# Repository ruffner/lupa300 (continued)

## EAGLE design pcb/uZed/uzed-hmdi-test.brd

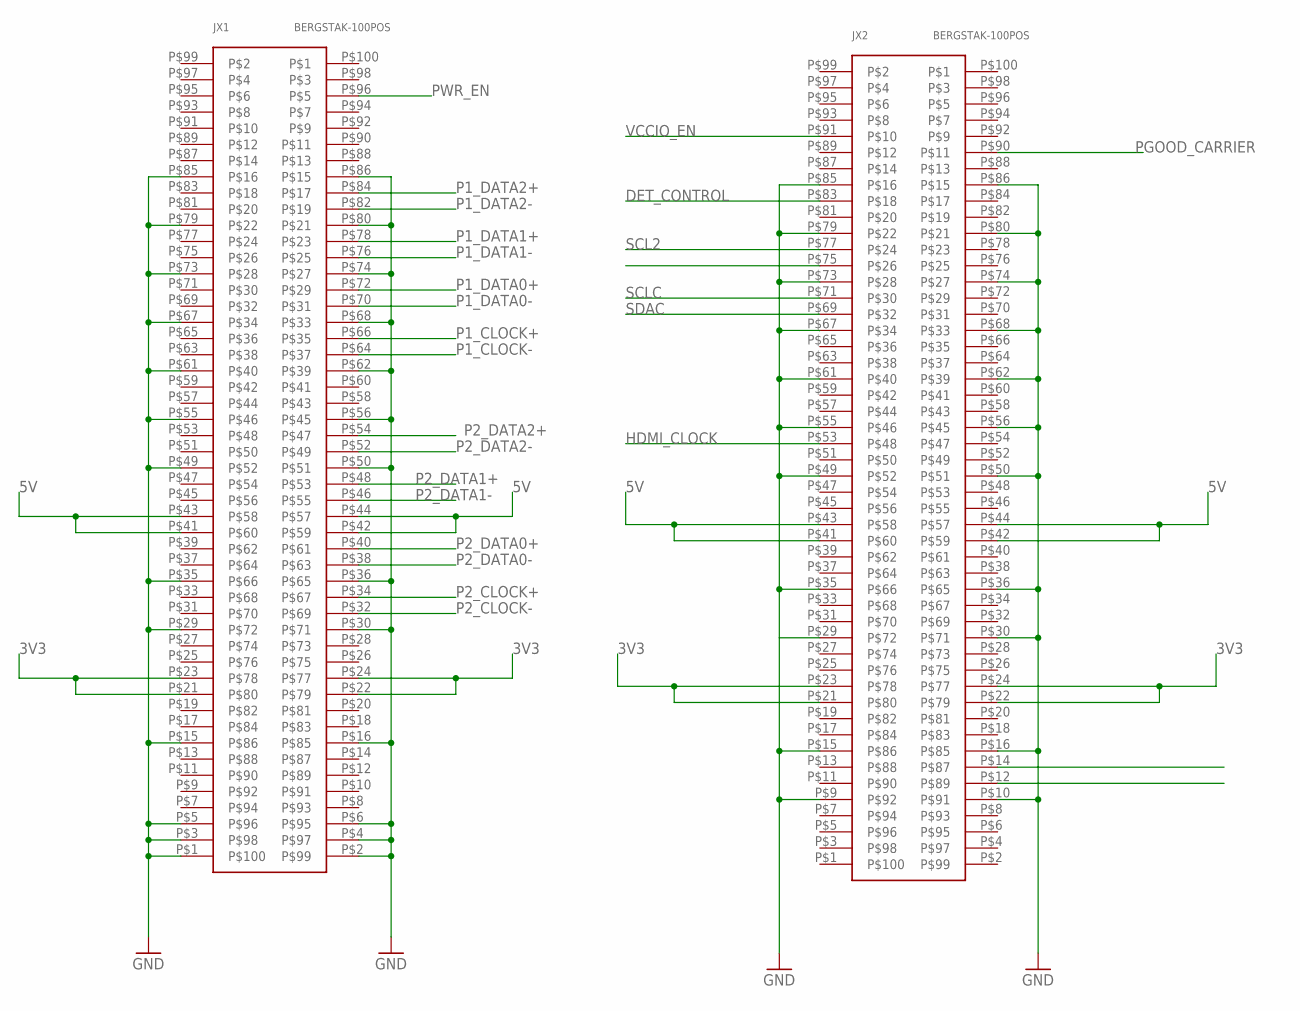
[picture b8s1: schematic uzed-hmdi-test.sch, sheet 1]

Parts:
JX1, JX2: BERGSTAK-100POS; BERG100POS

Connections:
3V3: JX1.P$21, JX1.P$22, JX1.P$23, JX1.P$24, JX2.P$21, JX2.P$22, JX2.P$23, JX2.P$24; also elsewhere on the board
5V: JX1.P$41, JX1.P$42, JX1.P$43, JX1.P$44, JX2.P$41, JX2.P$42, JX2.P$43, JX2.P$44; also elsewhere on the board
DET_CONTROL: JX2.P$83; also elsewhere on the board
GND: JX1.P$1, JX1.P$2, JX1.P$3, JX1.P$4, JX1.P$5, JX1.P$6, JX1.P$15, JX1.P$16, JX1.P$29, JX1.P$30, JX1.P$35, JX1.P$36, JX1.P$49, JX1.P$50, JX1.P$55, JX1.P$56, JX1.P$61, JX1.P$62, JX1.P$67, JX1.P$68, JX1.P$73, JX1.P$74, JX1.P$79, JX1.P$80, JX1.P$85, JX1.P$86, JX2.P$9, JX2.P$10, JX2.P$15, JX2.P$16, JX2.P$29, JX2.P$30, JX2.P$35, JX2.P$36, JX2.P$49, JX2.P$50, JX2.P$55, JX2.P$56, JX2.P$61, JX2.P$62, JX2.P$67, JX2.P$68, JX2.P$73, JX2.P$74, JX2.P$79, JX2.P$80, JX2.P$85, JX2.P$86; also elsewhere on the board
HDMI_CLOCK: JX2.P$53; also elsewhere on the board
P1_CLOCK+: JX1.P$66; also elsewhere on the board
P1_CLOCK-: JX1.P$64; also elsewhere on the board
P1_DATA0+: JX1.P$72; also elsewhere on the board
P1_DATA0-: JX1.P$70; also elsewhere on the board
P1_DATA1+: JX1.P$78; also elsewhere on the board
P1_DATA1-: JX1.P$76; also elsewhere on the board
P1_DATA2+: JX1.P$84; also elsewhere on the board
P1_DATA2-: JX1.P$82; also elsewhere on the board
P2_CLOCK+: JX1.P$34; also elsewhere on the board
P2_CLOCK-: JX1.P$32; also elsewhere on the board
P2_DATA0+: JX1.P$40; also elsewhere on the board
P2_DATA0-: JX1.P$38; also elsewhere on the board
P2_DATA1+: JX1.P$48; also elsewhere on the board
P2_DATA1-: JX1.P$46; also elsewhere on the board
P2_DATA2+: JX1.P$54; also elsewhere on the board
P2_DATA2-: JX1.P$52; also elsewhere on the board
PGOOD_CARRIER: JX2.P$90
PWR_EN: JX1.P$96
SCL2: JX2.P$77; also elsewhere on the board
SCLC: JX2.P$71; also elsewhere on the board
SDA2: JX2.P$75; also elsewhere on the board
SDAC: JX2.P$69; also elsewhere on the board
VCCIO_EN: JX2.P$91

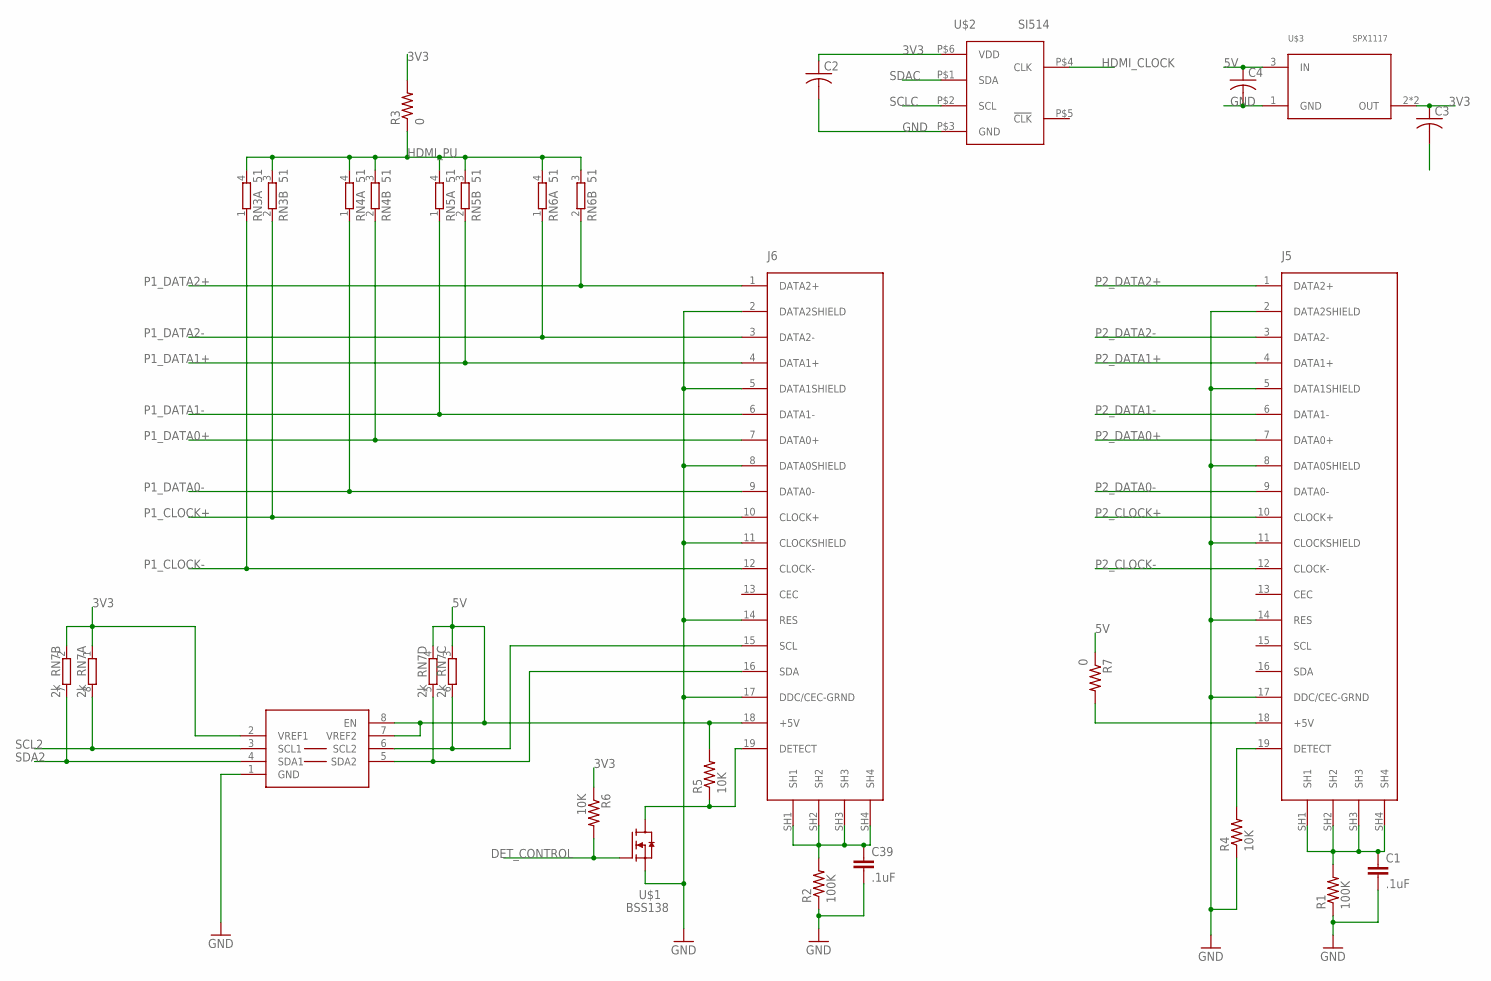
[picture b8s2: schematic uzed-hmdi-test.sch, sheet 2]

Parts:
C1, C39: .1uF; C0603K
C2, C3, C4: C-USC0603; C0603
J5, J6: HDMI-TYPE-A-RECEPTICALFCI10029449; FCI-HDMI-TYPE-A-RECEPT
PCA9306: PCA9306; PSOP-8
R1, R2: 100K; R0603
R3, R7: 0; R0603
R4, R5, R6: 10K; R0603
RN3, RN4, RN5, RN6: 51; EXB34V
RN7: 2k; 0603-ARV
U$1: BSS138; SOT23
U$2: SI514; XTAL-6PIN
U$3: SPX1117; SOT223

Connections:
3V3: C2.1, C3.1, PCA9306.2 (VREF1), R3.2, R6.1, RN7.1, RN7.2 (1), U$2.P$6 (VDD), U$3.2 (OUT), U$3.4 (OUT); also elsewhere on the board
5V: C4.1, J6.18 (+5V), PCA9306.7 (VREF2), PCA9306.8 (EN), R5.2, R7.1, RN7.3 (1), RN7.4 (1), U$3.3 (IN); also elsewhere on the board
DET_CONTROL: R6.2, U$1.1 (G); also elsewhere on the board
GND: C1.2, C2.2, C3.2, C4.2, C39.2, J5.2 (DATA2SHIELD), J5.5 (DATA1SHIELD), J5.8 (DATA0SHIELD), J5.11 (CLOCKSHIELD), J5.14 (RES), J5.17 (DDC/CEC-GRND), J6.2 (DATA2SHIELD), J6.5 (DATA1SHIELD), J6.8 (DATA0SHIELD), J6.11 (CLOCKSHIELD), J6.14 (RES), J6.17 (DDC/CEC-GRND), PCA9306.1 (GND), R1.1, R2.1, R4.1, U$1.2 (S), U$2.P$3 (GND), U$3.1 (GND); also elsewhere on the board
HDMI_CLOCK: U$2.P$4 (CLK); also elsewhere on the board
HDMI_PU: R3.1, RN3.3 (2), RN3.4 (2), RN4.3 (2), RN4.4 (2), RN5.3 (2), RN5.4 (2), RN6.3 (2), RN6.4 (2)
unnamed: C1.1, J5.SH1, J5.SH2, J5.SH3, J5.SH4, R1.2
unnamed: J5.19 (DETECT), R4.2
unnamed: J6.19 (DETECT), R5.1, U$1.3 (D)
unnamed: J5.18 (+5V), R7.2
unnamed: J6.16 (SDA), PCA9306.5 (SDA2), RN7.5 (2)
unnamed: J6.15 (SCL), PCA9306.6 (SCL2), RN7.6 (2)
unnamed: C39.1, J6.SH1, J6.SH2, J6.SH3, J6.SH4, R2.2
P1_CLOCK+: J6.10 (CLOCK+), RN3.2 (1); also elsewhere on the board
P1_CLOCK-: J6.12 (CLOCK-), RN3.1; also elsewhere on the board
P1_DATA0+: J6.7 (DATA0+), RN4.2 (1); also elsewhere on the board
P1_DATA0-: J6.9 (DATA0-), RN4.1; also elsewhere on the board
P1_DATA1+: J6.4 (DATA1+), RN5.2 (1); also elsewhere on the board
P1_DATA1-: J6.6 (DATA1-), RN5.1; also elsewhere on the board
P1_DATA2+: J6.1 (DATA2+), RN6.2 (1); also elsewhere on the board
P1_DATA2-: J6.3 (DATA2-), RN6.1; also elsewhere on the board
P2_CLOCK+: J5.10 (CLOCK+); also elsewhere on the board
P2_CLOCK-: J5.12 (CLOCK-); also elsewhere on the board
P2_DATA0+: J5.7 (DATA0+); also elsewhere on the board
P2_DATA0-: J5.9 (DATA0-); also elsewhere on the board
P2_DATA1+: J5.4 (DATA1+); also elsewhere on the board
P2_DATA1-: J5.6 (DATA1-); also elsewhere on the board
P2_DATA2+: J5.1 (DATA2+); also elsewhere on the board
P2_DATA2-: J5.3 (DATA2-); also elsewhere on the board
SCL2: PCA9306.3 (SCL1), RN7.8 (2); also elsewhere on the board
SCLC: U$2.P$2 (SCL); also elsewhere on the board
SDA2: PCA9306.4 (SDA1), RN7.7 (2); also elsewhere on the board
SDAC: U$2.P$1 (SDA); also elsewhere on the board

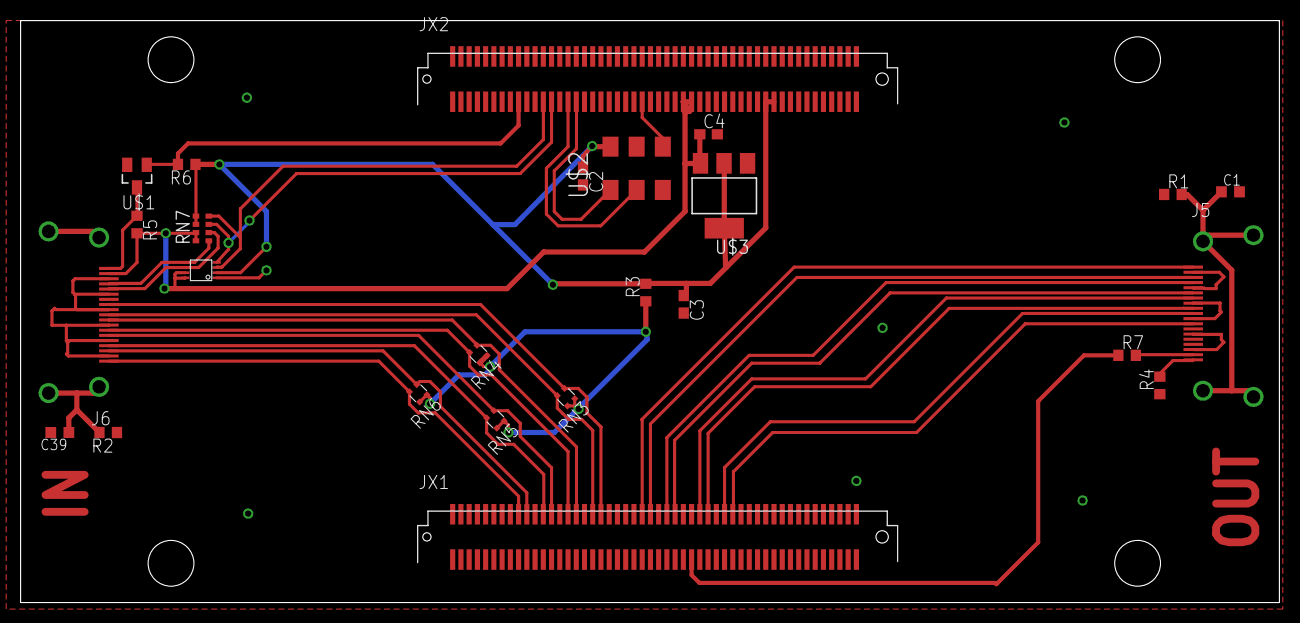
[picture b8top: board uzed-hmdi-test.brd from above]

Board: 2 copper layers, 122.2 x 56.5 mm, 25 parts (0 on the bottom side), 33 nets.

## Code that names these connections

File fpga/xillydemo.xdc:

# There are no constraints in this XDC file, because
#
# (a) the only clock in the system is generated by the processor part, and
#     it's already constrained through generated XDCs, and
# (b) there are no pin placements, since the board has nothing connected to
#     the PL pins, except for general-purpose expansion connectors.


set_property IOSTANDARD LVCMOS25 [get_ports {DATA_IMAGE[9]}]
set_property IOSTANDARD LVCMOS25 [get_ports {DATA_IMAGE[8]}]
set_property IOSTANDARD LVCMOS25 [get_ports {DATA_IMAGE[7]}]
set_property IOSTANDARD LVCMOS25 [get_ports {DATA_IMAGE[6]}]
set_property IOSTANDARD LVCMOS25 [get_ports {DATA_IMAGE[5]}]
set_property IOSTANDARD LVCMOS25 [get_ports {DATA_IMAGE[4]}]
set_property IOSTANDARD LVCMOS25 [get_ports {DATA_IMAGE[3]}]
set_property IOSTANDARD LVCMOS25 [get_ports {DATA_IMAGE[2]}]
set_property IOSTANDARD LVCMOS25 [get_ports {DATA_IMAGE[1]}]
set_property IOSTANDARD LVCMOS25 [get_ports {DATA_IMAGE[0]}]
set_property PACKAGE_PIN R19 [get_ports {DATA_IMAGE[9]}]
set_property PACKAGE_PIN T11 [get_ports {DATA_IMAGE[8]}]
set_property PACKAGE_PIN T12 [get_ports {DATA_IMAGE[7]}]
set_property PACKAGE_PIN T10 [get_ports {DATA_IMAGE[6]}]
set_property PACKAGE_PIN T19 [get_ports {DATA_IMAGE[5]}]
set_property PACKAGE_PIN U12 [get_ports {DATA_IMAGE[4]}]
set_property PACKAGE_PIN V12 [get_ports {DATA_IMAGE[3]}]
set_property PACKAGE_PIN U13 [get_ports {DATA_IMAGE[2]}]
set_property IOSTANDARD LVCMOS25 [get_ports FRAME_VALID]
set_property IOSTANDARD LVCMOS33 [get_ports INT_TIME1]
set_property IOSTANDARD LVCMOS33 [get_ports INT_TIME2]
set_property IOSTANDARD LVCMOS33 [get_ports INT_TIME3]
set_property IOSTANDARD LVCMOS25 [get_ports LINE_VALID]
set_property IOSTANDARD LVCMOS33 [get_ports LUPA_CLK]
set_property IOSTANDARD LVCMOS33 [get_ports LUPA_RST]
set_property IOSTANDARD LVCMOS25 [get_ports SPI_CLK]
set_property IOSTANDARD LVCMOS25 [get_ports SPI_DAT]
set_property IOSTANDARD LVCMOS25 [get_ports SPI_EN]
set_property PACKAGE_PIN C20 [get_ports LUPA_RST]
set_property PACKAGE_PIN D20 [get_ports LUPA_CLK]
set_property PACKAGE_PIN P14 [get_ports FRAME_VALID]
set_property PACKAGE_PIN T15 [get_ports LINE_VALID]


set_property PACKAGE_PIN Y16 [get_ports SPI_EN]
set_property PACKAGE_PIN W14 [get_ports SPI_CLK]
set_property PACKAGE_PIN Y17 [get_ports SPI_DAT]


set_property IOSTANDARD LVCMOS25 [get_ports {LED_debug[3]}]
set_property IOSTANDARD LVCMOS25 [get_ports {LED_debug[2]}]
set_property IOSTANDARD LVCMOS25 [get_ports {LED_debug[1]}]
set_property IOSTANDARD LVCMOS25 [get_ports {LED_debug[0]}]


set_property PACKAGE_PIN B19 [get_ports INT_TIME1]


set_property PACKAGE_PIN B20 [get_ports INT_TIME2]
set_property PACKAGE_PIN A20 [get_ports INT_TIME3]





set_property CLOCK_DEDICATED_ROUTE FALSE [get_nets FRAME_VALID_IBUF]
set_property CLOCK_DEDICATED_ROUTE FALSE [get_nets LINE_VALID_IBUF]
















set_property PULLUP true [get_ports LINE_VALID]
set_property PULLUP true [get_ports FRAME_VALID]




















set_property PULLUP true [get_ports SPI_CLK]
set_property PULLUP true [get_ports SPI_DAT]
set_property PULLUP true [get_ports SPI_EN]


set_property PACKAGE_PIN T16 [get_ports {LED_debug[0]}]
set_property PACKAGE_PIN V15 [get_ports {LED_debug[1]}]
set_property PACKAGE_PIN U17 [get_ports {LED_debug[2]}]
set_property PACKAGE_PIN W15 [get_ports {LED_debug[3]}]

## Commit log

2017-08-30 added pcb and lens mount
2017-08-31 setup inital firmware
2017-08-31 added pin defs
2017-12-05 started new breakout board
2017-12-06 more work on breakout
2017-12-07 finished lupa breakout
2017-12-08 increased via pad size
2017-12-08 made passices 1206 form factor
2017-12-08 started on lupa carrier:
2017-12-14 work on carrier
2017-12-14 work on lup breakout
2017-12-14 added newer soft start board for pin reference, removed old dual header design
2017-12-14 finalized breakout for lupa module
2017-12-14 finished with uZed carrier board.
2017-12-14 added image of dimensioned breakout board
2017-12-14 bare bones qt application working
2017-12-15 made vias smaller and fixed silkscreen
2017-12-15 fixed silkscreen
2017-12-15 started carrier board for teensy
2017-12-19 finished teensy carrier and added image of dimensions
2017-12-20 updated pin defs for teensy_carrier board
2018-01-19 updated lens mount
2018-01-19 created lupa sensor protective cover
2018-01-19 added mosfet for fpga control of board power
2018-01-25 added fixed focal length lens moount
2018-02-01 added new camera shield
2018-02-02 finished new camera shield
2018-02-03 started v2 lupa breakout, for microzed sbc
2018-02-04 more work on lupa card
2018-02-04 made lupa card 4 layer
2018-02-04 finished prelim routing.
2018-02-05 routed critical signals.
2018-02-05 finalized design
2018-02-05 added references and BOM for new 4 layer lupa card order
2018-02-06 removed eagle library backup files
2018-02-13 added bergstak 100 pin connector to eagle library and started uzed hdmi shield
2018-02-19 added all component values and added partslist
2018-03-02 added new pluto fpga camer trigger shield
2018-03-05 made a home for all the cad
2018-03-06 updated pluto enclosure
2018-03-06 prog xtal breakout and work on hdmi board
2018-03-07 reorganized pcb folder
2018-03-08 moved lupa300 card
2018-03-09 added stl folder for lens mounts and added c mount bracket for the lupa300-card pcb
2018-03-13 upate trigger shield
2018-03-13 added pca9306 breakout
2018-03-18 added new board design
2018-03-19 added si514 programmer
2018-03-20 added code to program 73.25Mhz to xo. untested
2018-03-20 added new voltage regulators
2018-03-20 73.25 MHZ programming code verified, made general programming function
2018-03-21 more work
2018-03-25 added adc output buffer
2018-03-26 added separate ground planes
2018-03-26 added buffer
2018-03-28 hdmi connections copied in from scarab hardware board
2018-03-30 hdmi added in from scarab board
2018-03-30 added spdt switch and new n channel mosfet
2018-03-30 more work on hdmi, layout with mounting holes complete, bergstak connectors aligned to be to carrier board spec
2018-03-30 added reference layout documents and oder csv list
2018-03-30 added bergstak dimensional drawing
2018-03-30 added uZed carrier design guide
2018-03-30 improved register generating code. 73.5MHz is correct clock for 120.00 Hz video
2018-03-30 added minispartan reference designs
2018-04-04 added basler board
2018-04-04 added text
2018-04-06 started 2 layer hdmi test board
2018-04-09 more work on hdmi -test
2018-04-09 full sized hdmi test
2018-04-09 finished hdmi test board
2018-04-10 added pin connections for hdmi test board
2018-04-12 cleaned up and added more comments
2018-04-17 added mojo reference library
2018-04-17 added mojo basler begin
2018-04-18 finished basler camera adapter shield for mojo fpga board
2018-04-23 started dual basler shield for the mojo
2018-04-30 switched to full coverage shield with new pinouts
2018-05-07 added git ignore
2018-05-08 dual basler shield circuit complete
2018-05-08 dual basler shield silkscreen edit
2018-05-08 added manta manual for pinout
2018-05-08 added basler manual
2018-05-14 added lau logo
2018-05-14 started avt trigger board
2018-05-15 finished avt trigger board
2018-05-15 fixed pin assignments
2018-05-21 added test carrier design
2018-05-21 added new components for carrier board
2018-05-21 more work on carrier test
2018-05-21 more carrier card components added
2018-05-22 tweaked layout, ready to fab
2018-05-31 added 2A 3.3v reg to power suply design. made power supply layout more compact. increased board size
2018-06-01 more lupa crrier layout work
2018-06-02 almost done routing
2018-06-04 finished improved power supply layout
2018-06-04 arranged silk screen text.
2018-06-04 ordered 5 from pcbway as is
2018-06-05 started lupa300 integration, converted to 4 layer
2018-06-05 added andon library for lupa300 socket
2018-06-05 layout out power for lupa
2018-06-06 added low noise regulators for sensitive lupa supplys
2018-06-12 layed out regualtors for lupa power
2018-06-19 more work on power supply to lupa
2018-06-19 more work on power routing
2018-06-20 started clock and data pin routing
2018-06-27 more work on power dist
2018-06-28 control lines layed out. pdn complete.
2018-06-29 almost ready for fab
2018-07-02 ordered from pcbway
2018-07-17 added partslist for lupa carrier board
2018-07-23 added lupa-carrier cover and lens mount
2018-07-26 added hdmi connectors, routing in progress
2018-07-27 started hdmi integration. removed dot in drill layer in andon socket
2018-07-27 length tuned hdmi in traces
2018-07-27 added images to analyze fpn
2018-08-01 added stripped down tcp video streaming
2018-08-01 resolved qtzerconf issue on debian
2018-08-01 explained reason for not deleting zconf object
2018-08-01 added eagle temporary library files
2018-08-01 added lupa tcp video server code
2018-08-01 removed dup source file defs
2018-08-01 Fixes for Mac OS X.
2018-08-02 Lot's of fixes for Mac that should be ported over to the zedboard.
2018-08-02 Replaced LAUMemoryObject with an updated version. I also implemented grabbing blocks of video frames instead of one at a time.
2018-08-02 Just implemented the code that let's us control how fast the client asks for frames. Just look at the bottom of the tcp client class inside the method void LAU3DVideoTCPClient::onUpdateBuffer(LAUMemo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
2018-08-02 fix for zedboard
2018-08-02 actually reverted memoryobjects
2018-08-02 length tuning
2018-08-02 more debugging statements for zed
2018-08-02 added fpn capture
2018-08-03 changed frame grab trigger
2018-08-03 remove erroneous qfile
2018-08-03 added xillybus fifo demo
2018-08-03 ./uzedfpga_yyu226/
2018-08-03 cleanup
2018-08-03 added verilog code for uZed FPGA
2018-08-03 removed unnecessary file desc
2018-08-05 slowed frame rate
2018-08-06 implemented threaded fifo reading in onUpdateBuffer()
2018-08-06 static var fix
2018-08-06 fixes for uZed
2018-08-06 added static fifo initializer
2018-08-22 added start of ajile dmd <-> ximea camera interface pcb
2018-08-23 finished trigger adapter board
2018-08-23 move files
2018-08-24 put barrel jack on other side
2018-08-29 started Mojo loader tool to integrate EEPROM flashing
2018-08-29 added existing python code
2018-08-29 added numbered image generator
2018-08-29 added original python jupyter notebook and LUT text file
2018-08-30 more work on gui for ojo uploader
2018-08-31 eeprom upload implemented, untested
2018-08-31 uploading to eeprom functional
2018-09-12 added LAUMEM lut readability
2018-09-12 final python code
2018-09-17 added more dimensions
2018-09-17 updated with schematic
2018-09-18 beginning 4 layer hdmi board, discarded 6 layer approach
2018-09-18 routed hdmi and lupa data lines
2018-09-18 more layout
2018-09-19 lupa control signals routed
2018-09-19 added dimensioned carrier main part placement
2018-09-19 finished component layout
2018-09-19 routing completed. needs double check before ordering from fab
2018-09-20 gnd via tweaks. need to organize silkscreen component names
2018-09-21 finished silk screen layout
2018-09-21 more gnd vias under hdmi
2018-09-21 slight modification to powerup circuitry
2018-09-25 added cassi pushbroom pattern matlab generating code
2018-09-25 added raw image from lupa sensor
2018-09-25 ignore qt .pro.user files
2018-09-25 removed mojo uploader, now managed in 3dvideorecorder
2018-09-28 inverted colors for dmd
2018-09-28 added white/black cal
2018-10-02 centered pushbroom patterns
2018-10-02 removed old scripts
2018-10-04 added high frequency patterns at corners of calibration images.
2018-10-04 added programmable oscillator datasheet
2018-10-05 updated microzed pinout tables with new hdmi carrier connections
2018-10-15 cleaned up pcb folder. added images of pcbs
2018-10-15 cleanup and add mojo image
2018-10-15 removed old cad files
2018-10-15 better pic of front
2018-10-16 rotated back image
2018-10-16 added carrier layout image
2018-10-16 rm layout
2018-10-16 cropped
2018-10-16 added ground/power planes
2018-11-09 added images and silkscreen tweaks on pcb layout. fixed cap lableling.
2018-12-05 added new images used in thesis
2018-12-05 added grid patgen start
2018-12-06 grid pattern generation done. need ajile project now
2018-12-06 added repeater script for ajile frames
2018-12-12 fix for ajile - must be RGB image
2018-12-12 added script to repair ajile xml project file once it has been moved within a filesystem
2018-12-12 added name and date to the scipt
2018-12-12 added picoblade footprint
2018-12-13 finished new ajile adapter pcb and added libraries used
2018-12-19 added footprint
2018-12-19 started new basler mojo pcb with molex
2018-12-19 routed new mojo board
2018-12-19 added material used in thesis that was originally exlcuded
2019-01-02 finished basler shield v2
2019-01-02 added pcbway cam file
2019-01-02 added final revisions to ximea trigger board
2019-01-02 finished with basler shield v2
2019-01-02 added pcbway gerbers for basler shield v2
2019-01-15 added new pattern generating code and resuling images with correct polarity for dmd surface
2019-01-16 removed wrong size spacing patterns
2019-01-31 added buildPatterns function for pyramid patterns
2019-02-01 parseImage.m
2019-02-06 removed cassi work from this repo
2019-03-01 added old library changes
